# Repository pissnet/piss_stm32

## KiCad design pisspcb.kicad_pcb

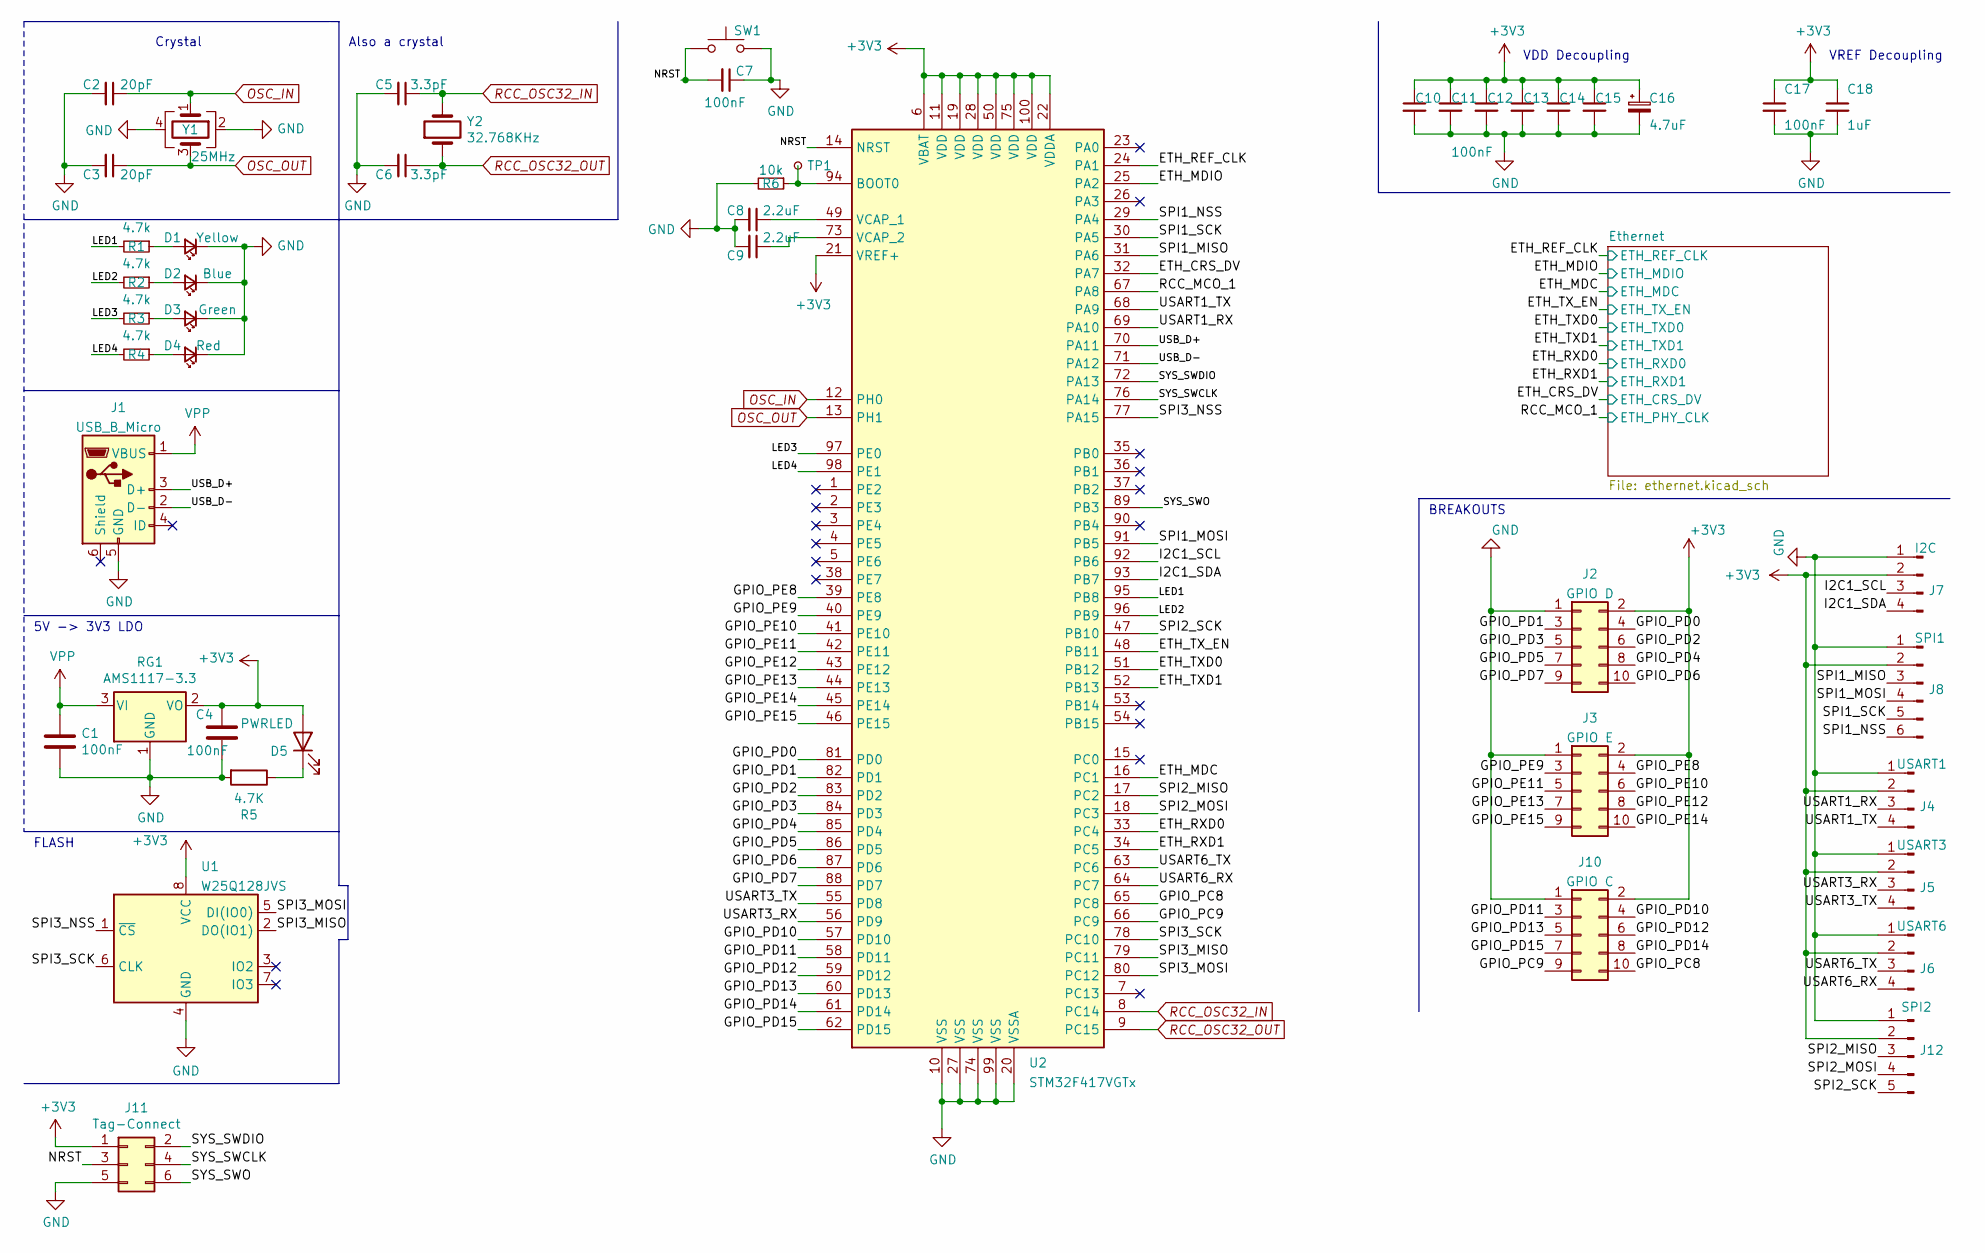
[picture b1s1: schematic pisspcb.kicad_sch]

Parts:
C1, C4: 100nF; C_0805_2012Metric; LCSC C49678
C2, C3: 20pF; C_0603_1608Metric; LCSC C1648
C5, C6: 3.3pF; C_0402_1005Metric; LCSC C1565
C7, C10, C11, C12, C13, C14, C15, C17: 100nF; C_0603_1608Metric; LCSC C14663
C8, C9: 2.2uF; C_0805_2012Metric; LCSC C49217
C16: 4.7uF; C_0805_2012Metric; LCSC C1779
C18: 1uF; C_0603_1608Metric; LCSC C15849
D1: Yellow; LED_0603_1608Metric; LCSC C72038
D2: Blue; LED_0603_1608Metric; LCSC C72041
D3: Green; LED_0603_1608Metric; LCSC C72043
D4: Red; LED_0603_1608Metric; LCSC C2286
D5: PWRLED; LED_0603_1608Metric; LCSC C2286
J1: USB_B_Micro; USB_Micro-B_Amphenol_10118194_Horizontal; LCSC C132563
J2: GPIO D; PinHeader_2x05_P2.54mm_Vertical
J3: GPIO E; PinHeader_2x05_P2.54mm_Vertical
J4: USART1; PinHeader_1x04_P2.54mm_Vertical
J5: USART3; PinHeader_1x04_P2.54mm_Vertical
J6: USART6; PinHeader_1x04_P2.54mm_Vertical
J7: I2C; PinHeader_1x04_P2.54mm_Vertical
J8: SPI1; PinHeader_1x06_P2.54mm_Vertical
J10: GPIO C; PinHeader_2x05_P2.54mm_Vertical
J11: Tag-Connect; Tag-Connect_TC2030-IDC-FP_2x03_P1.27mm_Vertical
J12: SPI2; PinHeader_1x05_P2.54mm_Vertical
R1, R2, R3, R4: 4.7k; R_0603_1608Metric; LCSC C23162
R5: 4.7K; R_0603_1608Metric; LCSC C23162
R6: 10k; R_0603_1608Metric; LCSC C25804
RG1: AMS1117-3.3; SOT-223-3_TabPin2; LCSC C6186
SW1: SW_Push; SW_SPST_TL3342; LCSC C412370
TP1: BOOT0; TestPoint_Pad_D1.0mm
U1: W25Q128JVS; SOIC-8_5.23x5.23mm_P1.27mm; LCSC C97521
U2: STM32F417VGTx; LQFP-100_14x14mm_P0.5mm
Y1: 25MHz; Crystal_SMD_3225-4Pin_3.2x2.5mm; LCSC C9006
Y2: 32.768KHz; Crystal_SMD_3215-2Pin_3.2x1.5mm; LCSC C32346

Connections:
+3V3: C4.1, C10.1, C11.1, C12.1, C13.1, C14.1, C15.1, C16.1, C17.1, C18.1, D5.2 (A), J2.2, J3.2, J4.2, J5.2, J6.2, J7.2, J8.2, J10.2, J11.1, J12.2, RG1.2 (VO), U1.8 (VCC), U2.6 (VBAT), U2.11 (VDD), U2.19 (VDD), U2.21 (VREF+), U2.22 (VDDA), U2.28 (VDD), U2.50 (VDD), U2.75 (VDD), U2.100 (VDD); also elsewhere on the board
/ETH_CRS_DV: U2.32 (PA7); also elsewhere on the board
/ETH_MDC: U2.16 (PC1); also elsewhere on the board
/ETH_MDIO: U2.25 (PA2); also elsewhere on the board
/ETH_REF_CLK: U2.24 (PA1); also elsewhere on the board
/ETH_RXD0: U2.33 (PC4); also elsewhere on the board
/ETH_RXD1: U2.34 (PC5); also elsewhere on the board
/ETH_TXD0: U2.51 (PB12); also elsewhere on the board
/ETH_TXD1: U2.52 (PB13); also elsewhere on the board
/ETH_TX_EN: U2.48 (PB11); also elsewhere on the board
/GPIO_PC8: J10.10, U2.65 (PC8)
/GPIO_PC9: J10.9, U2.66 (PC9)
/GPIO_PD0: J2.4, U2.81 (PD0)
/GPIO_PD1: J2.3, U2.82 (PD1)
/GPIO_PD2: J2.6, U2.83 (PD2)
/GPIO_PD3: J2.5, U2.84 (PD3)
/GPIO_PD4: J2.8, U2.85 (PD4)
/GPIO_PD5: J2.7, U2.86 (PD5)
/GPIO_PD6: J2.10, U2.87 (PD6)
/GPIO_PD7: J2.9, U2.88 (PD7)
/GPIO_PD10: J10.4, U2.57 (PD10)
/GPIO_PD11: J10.3, U2.58 (PD11)
/GPIO_PD12: J10.6, U2.59 (PD12)
/GPIO_PD13: J10.5, U2.60 (PD13)
/GPIO_PD14: J10.8, U2.61 (PD14)
/GPIO_PD15: J10.7, U2.62 (PD15)
/GPIO_PE8: J3.4, U2.39 (PE8)
/GPIO_PE9: J3.3, U2.40 (PE9)
/GPIO_PE10: J3.6, U2.41 (PE10)
/GPIO_PE11: J3.5, U2.42 (PE11)
/GPIO_PE12: J3.8, U2.43 (PE12)
/GPIO_PE13: J3.7, U2.44 (PE13)
/GPIO_PE14: J3.10, U2.45 (PE14)
/GPIO_PE15: J3.9, U2.46 (PE15)
/I2C1_SCL: J7.3, U2.92 (PB6)
/I2C1_SDA: J7.4, U2.93 (PB7)
/LED1: R1.2, U2.95 (PB8)
/LED2: R2.2, U2.96 (PB9)
/LED3: R3.2, U2.97 (PE0)
/LED4: R4.2, U2.98 (PE1)
/NRST: C7.2, J11.3, SW1.1, U2.14 (NRST)
/RCC_MCO_1: U2.67 (PA8); also elsewhere on the board
/SPI1_MISO: J8.3, U2.31 (PA6)
/SPI1_MOSI: J8.4, U2.91 (PB5)
/SPI1_NSS: J8.6, U2.29 (PA4)
/SPI1_SCK: J8.5, U2.30 (PA5)
/SPI2_MISO: J12.3, U2.17 (PC2)
/SPI2_MOSI: J12.4, U2.18 (PC3)
/SPI2_SCK: J12.5, U2.47 (PB10)
/SPI3_MISO: U1.2 (DO(IO1)), U2.79 (PC11)
/SPI3_MOSI: U1.5 (DI(IO0)), U2.80 (PC12)
/SPI3_NSS: U1.1 (~CS), U2.77 (PA15)
/SPI3_SCK: U1.6 (CLK), U2.78 (PC10)
/SYS_SWCLK: J11.4, U2.76 (PA14)
/SYS_SWDIO: J11.2, U2.72 (PA13)
/SYS_SWO: J11.6, U2.89 (PB3)
/USART1_RX: J4.3, U2.69 (PA10)
/USART1_TX: J4.4, U2.68 (PA9)
/USART3_RX: J5.3, U2.56 (PD9)
/USART3_TX: J5.4, U2.55 (PD8)
/USART6_RX: J6.4, U2.64 (PC7)
/USART6_TX: J6.3, U2.63 (PC6)
/USB_D+: J1.3 (D+), U2.70 (PA11)
/USB_D-: J1.2 (D-), U2.71 (PA12)
GND: C1.2, C2.2, C3.2, C4.2, C5.2, C6.2, C7.1, C8.2, C9.2, C10.2, C11.2, C12.2, C13.2, C14.2, C15.2, C16.2, C17.2, C18.2, D1.1 (K), D2.1 (K), D3.1 (K), D4.1 (K), J1.5 (GND), J2.1, J3.1, J4.1, J5.1, J6.1, J7.1, J8.1, J10.1, J11.5, J12.1, R5.2, R6.2, RG1.1 (GND), SW1.2, U1.4 (GND), U2.10 (VSS), U2.20 (VSSA), U2.27 (VSS), U2.74 (VSS), U2.99 (VSS), Y1.2, Y1.4; also elsewhere on the board
unnamed: C8.1, U2.49 (VCAP_1)
unnamed: C9.1, U2.73 (VCAP_2)
unnamed: D1.2 (A), R1.1
unnamed: D2.2 (A), R2.1
unnamed: D3.2 (A), R3.1
unnamed: D4.2 (A), R4.1
unnamed: D5.1 (K), R5.1
unnamed: R6.1, TP1.1, U2.94 (BOOT0)
OSC_IN: C2.1, U2.12 (PH0), Y1.1
OSC_OUT: C3.1, U2.13 (PH1), Y1.3
RCC_OSC32_IN: C5.1, U2.8 (PC14), Y2.2
RCC_OSC32_OUT: C6.1, U2.9 (PC15), Y2.1
VPP: C1.1, J1.1 (VBUS), RG1.3 (VI)

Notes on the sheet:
Crystal
VREF Decoupling
VDD Decoupling
5V -> 3V3 LDO
Also a crystal
FLASH
BREAKOUTS

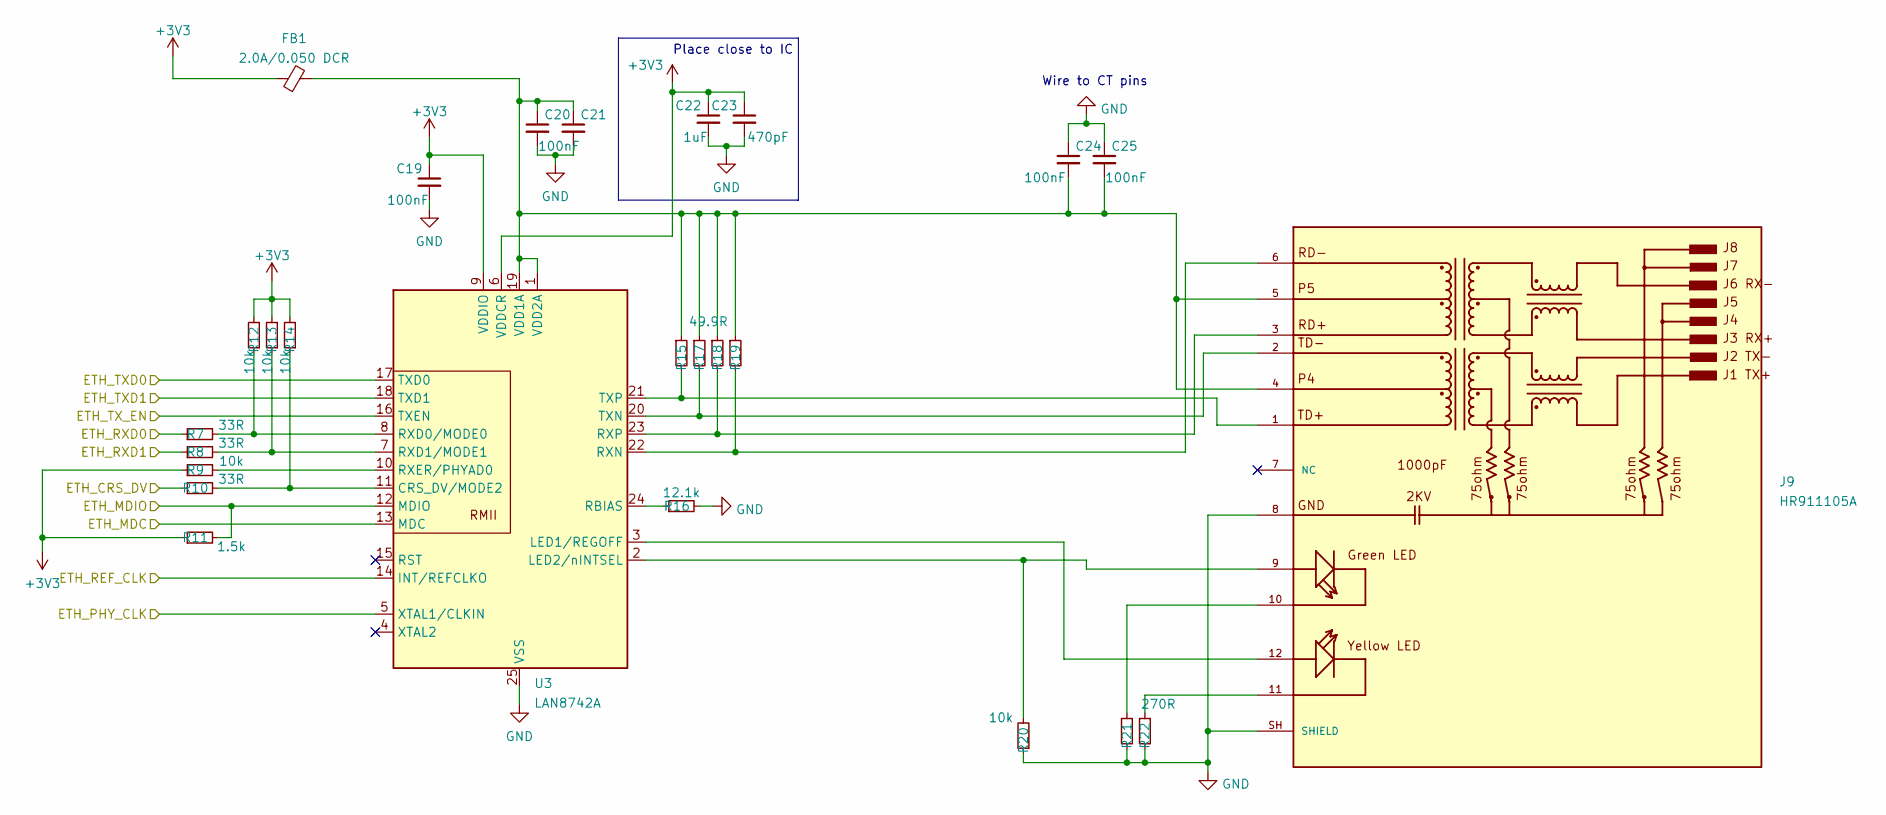
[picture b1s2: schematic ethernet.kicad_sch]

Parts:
C19, C20, C21, C24, C25: 100nF; C_0603_1608Metric
C22: 1uF; C_0603_1608Metric
C23: 470pF; C_0603_1608Metric
FB1: 2.0A/0.050 DCR; L_0805_2012Metric; LCSC C1015
J9: HR911105A; RJ45_Hanrun_HR911105A; PARTREV A
R7, R8, R10: 33R; R_0603_1608Metric; LCSC C23140
R9, R12, R13, R14, R20: 10k; R_0603_1608Metric
R11: 1.5k; R_0603_1608Metric
R15, R17, R18, R19: 49.9R; R_0603_1608Metric; LCSC C23185
R16: 12.1k; R_0603_1608Metric
R21, R22: 270R; R_0603_1608Metric; LCSC C22966
U3: LAN8742A; QFN-24-1EP_4x4mm_P0.5mm_EP2.6x2.6mm_ThermalVias

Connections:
+3V3: C19.1, C22.1, C23.1, FB1.1, R9.1, R11.1, R12.2, R13.2, R14.2, U3.6 (VDDCR), U3.9 (VDDIO); also elsewhere on the board
/ETH_CRS_DV: R10.1; also elsewhere on the board
/ETH_MDC: U3.13 (MDC); also elsewhere on the board
/ETH_MDIO: R11.2, U3.12 (MDIO); also elsewhere on the board
/ETH_REF_CLK: U3.14 (INT/REFCLKO); also elsewhere on the board
/ETH_RXD0: R7.1; also elsewhere on the board
/ETH_RXD1: R8.1; also elsewhere on the board
/ETH_TXD0: U3.17 (TXD0); also elsewhere on the board
/ETH_TXD1: U3.18 (TXD1); also elsewhere on the board
/ETH_TX_EN: U3.16 (TXEN); also elsewhere on the board
/RCC_MCO_1: U3.5 (XTAL1/CLKIN); also elsewhere on the board
GND: C19.2, C20.2, C21.2, C22.2, C23.2, C24.1, C25.1, J9.8, J9.SH (SHIELD), R16.2, R20.1, R21.2, R22.2, U3.25 (VSS); also elsewhere on the board
unnamed: C20.1, C21.1, C24.2, C25.2, FB1.2, J9.4, J9.5, R15.1, R17.1, R18.1, R19.1, U3.1 (VDD2A), U3.19 (VDD1A)
unnamed: J9.1, R15.2, U3.21 (TXP)
unnamed: J9.2, R17.2, U3.20 (TXN)
unnamed: J9.3, R18.2, U3.23 (RXP)
unnamed: J9.6, R19.2, U3.22 (RXN)
unnamed: J9.9, R20.2, U3.2 (LED2/nINTSEL)
unnamed: J9.10, R21.1
unnamed: J9.11, R22.1
unnamed: J9.12, U3.3 (LED1/REGOFF)
unnamed: R9.2, U3.10 (RXER/PHYAD0)
unnamed: R10.2, R14.1, U3.11 (CRS_DV/MODE2)
unnamed: R7.2, R12.1, U3.8 (RXD0/MODE0)
unnamed: R8.2, R13.1, U3.7 (RXD1/MODE1)
unnamed: R16.1, U3.24 (RBIAS)

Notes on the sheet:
Place close to IC
Wire to CT pins

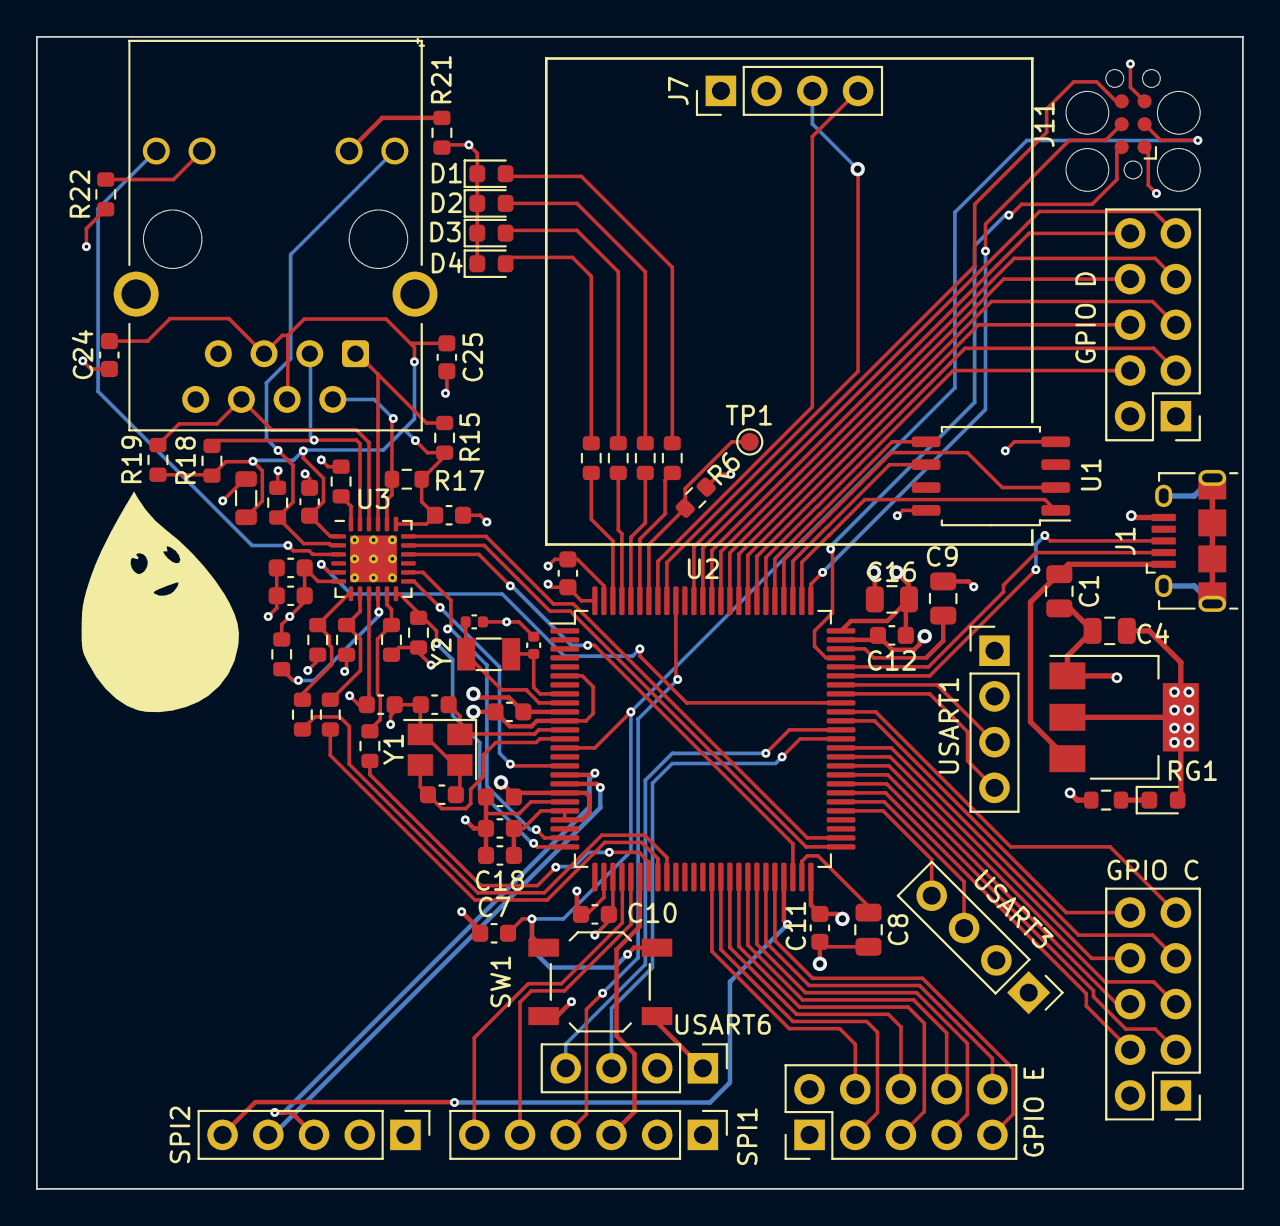
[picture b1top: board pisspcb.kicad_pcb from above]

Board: 4 copper layers, 67.0 x 64.0 mm, 73 parts (0 on the bottom side), 92 nets.
